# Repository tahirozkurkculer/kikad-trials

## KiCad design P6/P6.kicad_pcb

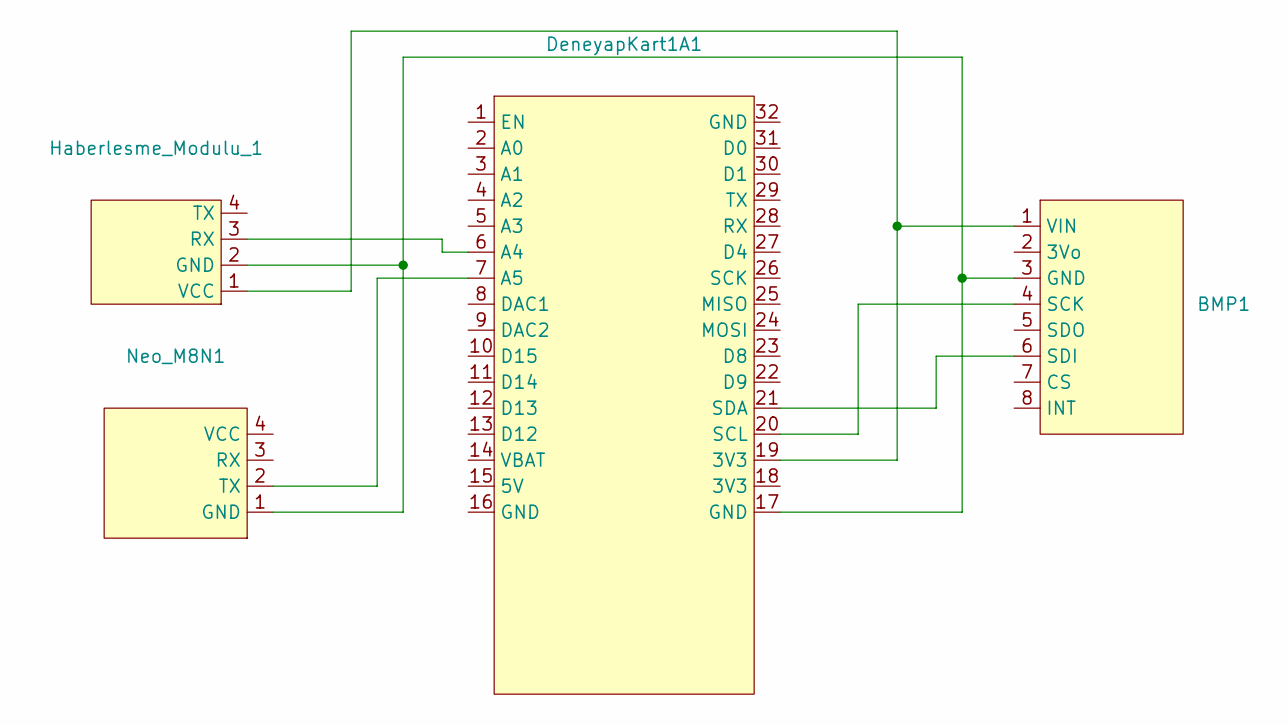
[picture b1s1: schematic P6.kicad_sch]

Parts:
BMP1: BMP388
DeneyapKart1A1: Deneyap 1A
Haberlesme_Modulu_1: Haberlesme_Modulu
Neo_M8N1: Neo M8N GPS

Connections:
unnamed: BMP1.3 (GND), DeneyapKart1A1.17 (GND), Haberlesme_Modulu_1.2 (GND), Neo_M8N1.1 (GND)
unnamed: BMP1.4 (SCK), DeneyapKart1A1.20 (SCL)
unnamed: BMP1.6 (SDI), DeneyapKart1A1.21 (SDA)
unnamed: BMP1.1 (VIN), DeneyapKart1A1.19 (3V3), Haberlesme_Modulu_1.1 (VCC)
unnamed: DeneyapKart1A1.6 (A4), Haberlesme_Modulu_1.3 (RX)
unnamed: DeneyapKart1A1.7 (A5), Neo_M8N1.2 (TX)

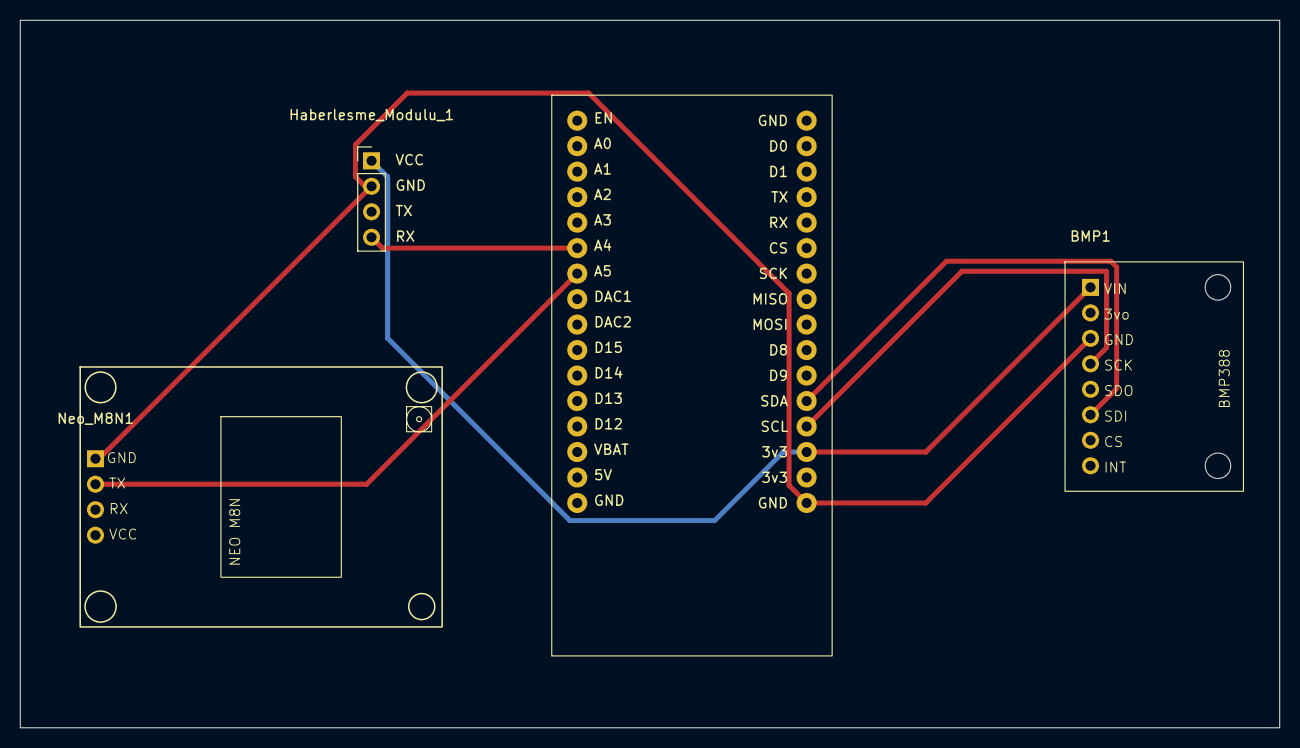
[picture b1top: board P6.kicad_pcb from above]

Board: 2 copper layers, 125.5 x 70.5 mm, 4 parts (0 on the bottom side), 6 nets.
